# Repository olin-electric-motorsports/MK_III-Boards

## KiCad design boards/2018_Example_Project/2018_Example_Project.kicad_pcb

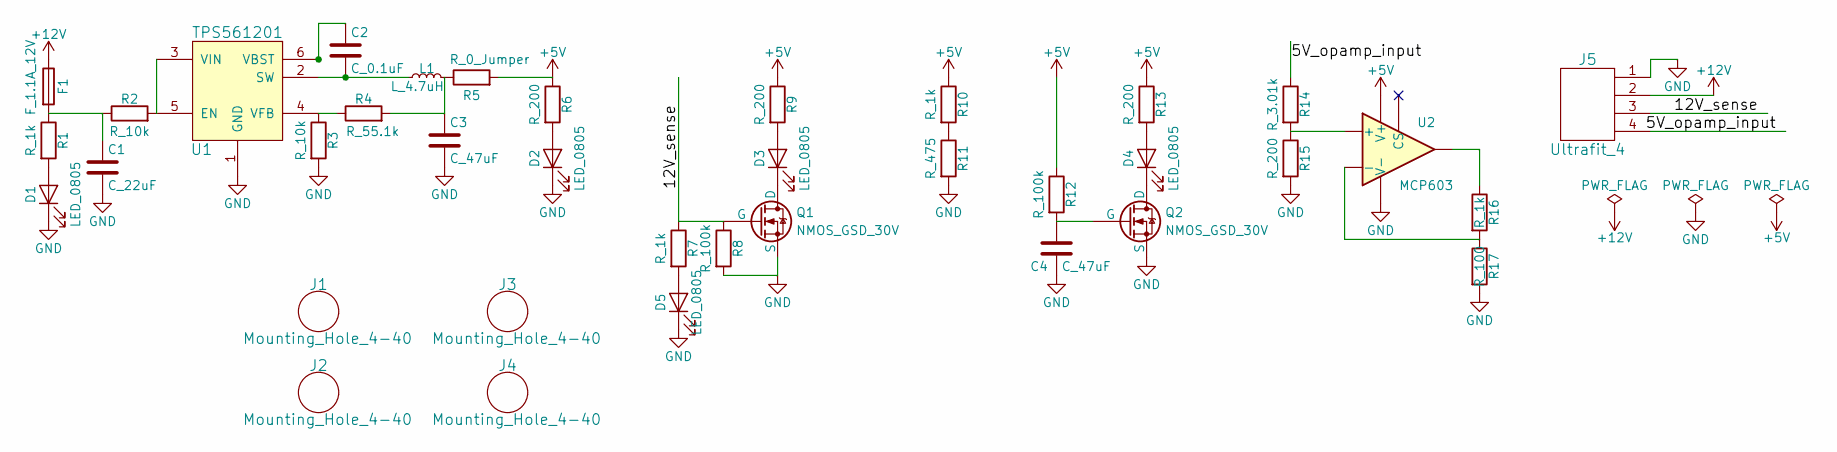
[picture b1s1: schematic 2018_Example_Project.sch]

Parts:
C1: C_22uF; C_1206; MPN 1276-2725-1-ND
C2: C_0.1uF; C_0805; MPN 478-3352-1-ND
C3, C4: C_47uF; C_0805; MPN 587-4280-1-ND
D1, D2, D3, D4, D5: LED_0805; MPN 475-1410-1-ND
F1: F_1.1A_12V; Fuse_SMD1206_Reflow; MPN F5764CT-ND
J1, J2, J3, J4: Mounting_Hole_4-40; MPN Value
J5: Ultrafit_4; MPN WM11574-ND
L1: L_4.7uH; 4.7uH_Inductor_OEM; MPN 445-6583-1-ND
Q1, Q2: NMOS_GSD_30V; SOT-23; MPN SSM3K333RLFCT-ND
R1, R7, R10, R16: R_1k; R_0805; MPN RNCP0805FTD1K00CT-ND
R2, R3: R_10k; R_0805; MPN CRS0805-FX-1002ELFCT-ND
R4: R_55.1k; R_0805; MPN 311-51.1KCRCT-ND
R5: R_0_Jumper; R_2512; MPN A121322CT-ND
R6, R9, R13, R15: R_200; R_0805; MPN RMCF0805JT200RCT-ND
R8, R12: R_100k; R_0805; MPN 311-100KCRCT-ND
R11: R_475; R_0805; MPN 311-475CRCT-ND
R14: R_3.01k; R_0805; MPN 311-3.01KCRCT-ND
R17: R_100; R_0805; MPN RNCP0805FTD100RCT-ND
U1: TPS561201; SOT-23-6; MPN TPS561201
U2: MCP603; SOT-23-6; MPN MCP603T-E/CHCT-ND

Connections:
+5V: R5.2, R6.1, R9.1, R10.1, R12.1, R13.1, U2.6 (V+)
+12V: F1.1, J5.2
/5V_opamp_input: J5.4, R14.1
/12V_sense: J5.3, Q1.1 (G), R7.1, R8.1
GND: C1.2, C3.2, C4.2, D1.1 (K), D2.1 (K), D5.1 (K), J5.1, Q1.2 (S), Q2.2 (S), R3.2, R8.2, R11.2, R15.2, R17.2, U1.1 (GND), U2.2 (V-)
unnamed: C1.1, F1.2, R1.1, R2.1
unnamed: C2.1, U1.6 (VBST)
unnamed: C2.2, L1.1, U1.2 (SW)
unnamed: C3.1, L1.2, R4.2, R5.1
unnamed: C4.1, Q2.1 (G), R12.2
unnamed: D1.2 (A), R1.2
unnamed: D2.2 (A), R6.2
unnamed: D3.1 (K), Q1.3 (D)
unnamed: D3.2 (A), R9.2
unnamed: D4.1 (K), Q2.3 (D)
unnamed: D4.2 (A), R13.2
unnamed: D5.2 (A), R7.2
unnamed: R2.2, U1.3 (VIN), U1.5 (EN)
unnamed: R3.1, R4.1, U1.4 (VFB)
unnamed: R10.2, R11.1
unnamed: R14.2, R15.1, U2.3 (+)
unnamed: R16.1, U2.1
unnamed: R16.2, R17.1, U2.4 (-)

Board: 2 copper layers, 37 parts (0 on the bottom side), 23 nets, no tracks yet.

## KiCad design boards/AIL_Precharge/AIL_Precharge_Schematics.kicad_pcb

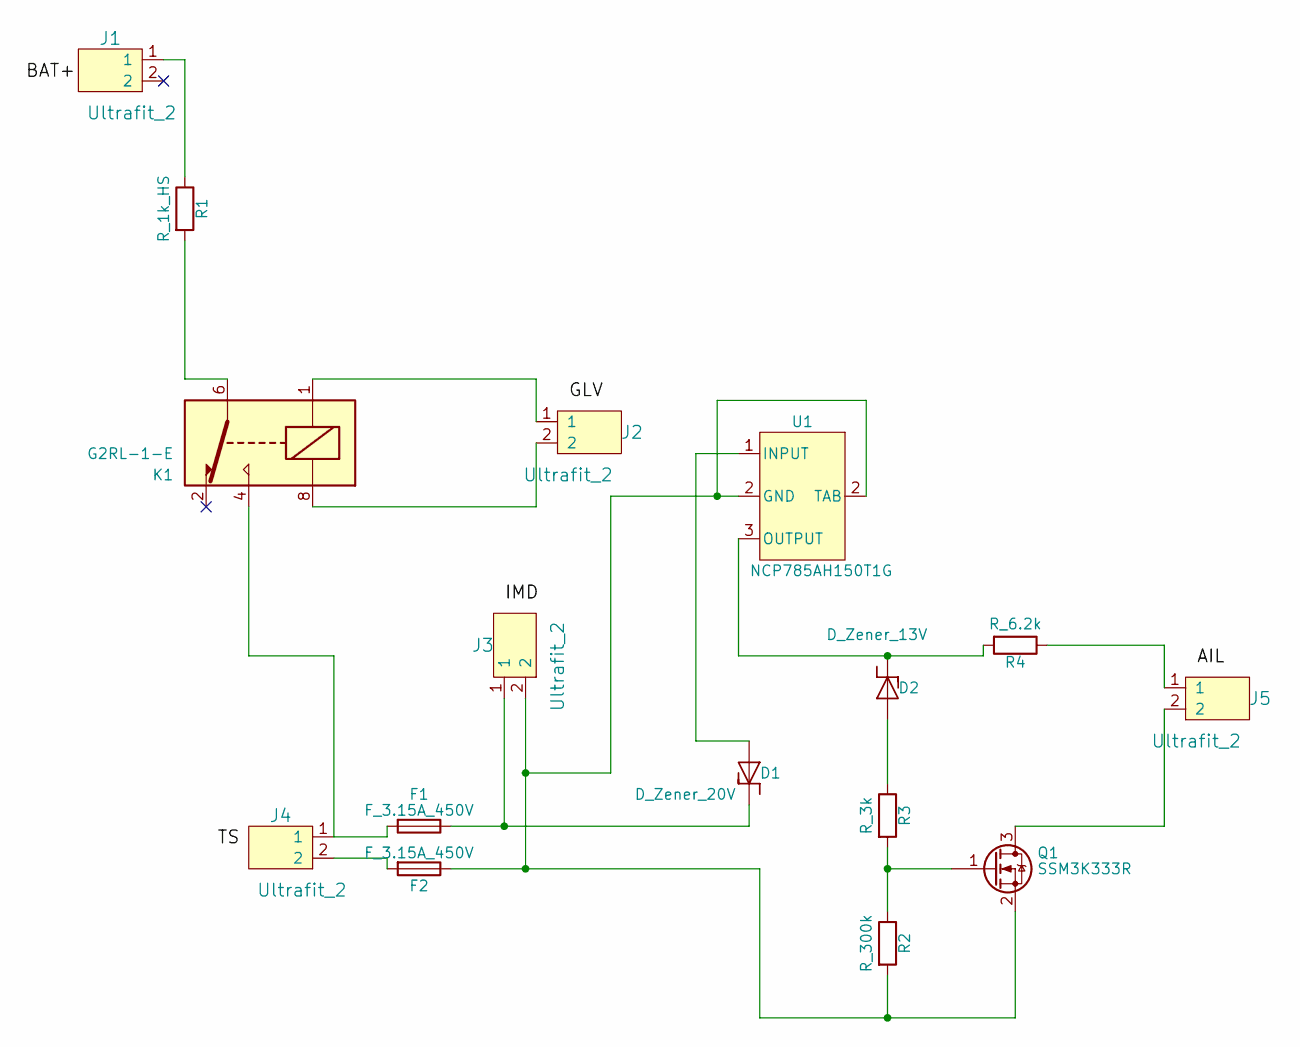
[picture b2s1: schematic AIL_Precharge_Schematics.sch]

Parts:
D1: D_Zener_20V; D_SOD-923; MPN CDZVT2R20BCT-ND
D2: D_Zener_13V; D_13V_Zener; MPN 1SMB5928BT3GOSCT-ND
F1, F2: F_3.15A_450V; Fuse_TE7_Littelfuse-807Series; MPN 80713150440
J1, J2, J3, J4, J5: Ultrafit_2; MPN WM11570-ND
K1: G2RL-1-E; Relay_SPDT_OMRON-G2RL-1-E; MPN Z2834-ND
Q1: SSM3K333R; SOT-23F; MPN SSM3K333RLFCT-ND
R1: R_1k_HS; R_1k_HS_TO247; MPN 696-1105-5-ND
R2: R_300k; R_0805_OEM; MPN P300KDACT-ND
R3: R_3k; R_0805_OEM; MPN RMCF0805FT3K00CT-ND
R4: R_6.2k; R_0805_OEM; MPN P6.20KCCT-ND
U1: NCP785AH150T1G; SOT-89-3; MPN NCP785AH150T1G

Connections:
unnamed: D1.1 (K), F1.1, J3.1
unnamed: D1.2 (A), U1.1 (INPUT)
unnamed: D2.1 (K), R4.2, U1.3 (OUTPUT)
unnamed: D2.2 (A), R3.1
unnamed: F1.2, J4.1, K1.4
unnamed: F2.1, J3.2, Q1.2 (S), R2.2, U1.2 (GND)
unnamed: F2.2, J4.2
unnamed: J1.1, R1.1
unnamed: J2.1, K1.1
unnamed: J2.2, K1.8
unnamed: J5.1, R4.1
unnamed: J5.2, Q1.3 (D)
unnamed: K1.6, R1.2
unnamed: Q1.1 (G), R2.1, R3.2

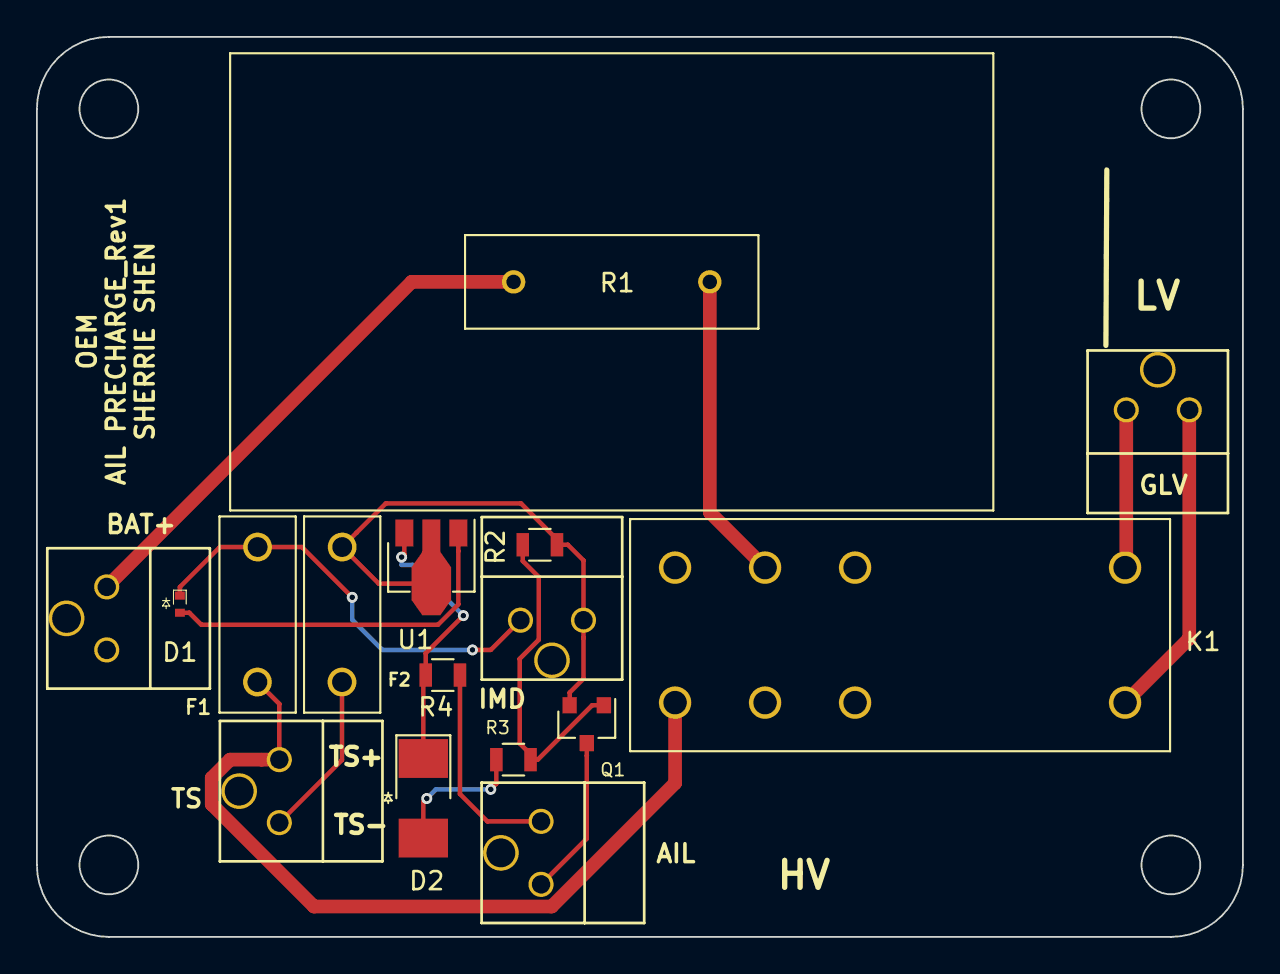
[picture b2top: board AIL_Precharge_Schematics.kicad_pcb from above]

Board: 2 copper layers, 67.0 x 50.0 mm, 16 parts (0 on the bottom side), 14 nets.

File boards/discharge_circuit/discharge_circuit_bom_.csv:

Component,Description,Part,References,Value,Footprint,Quantity Per PCB,Datasheet,MPN,MFN,PurchasingLink,Package,PurchasingLink2,MPN2
1,DIODE SCHOTTKY 100V 1A SOD123,D_Schottky_SOD123,D1,D_Schottky_SOD123,D_SOD-123W_OEM,1,https://assets.nexperia.com/documents/data-sheet/PMEG10010ELR.pdf,1727-2394-1-ND,Digi-Key,https://www.digikey.com/product-detail/en/nexperia-usa-inc/P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,,,
2,,F_3.15A_450V,F1 F2,F_3.15A_450V,Fuse_TE7_Littelfuse-807Series,2,http://www.mouser.com/ds/2/240/Littelfuse_Fuse_807_Datasheet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,80713150440,Mouser,https://www.mouser.com/ProductDetail/Littelfuse/80713150440/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,Value,,
3,ULTRAFIT CONN HDR 02CKT,Ultrafit_2,J2,Shutdown Circuit,Ultrafit_2,1,,WM11570-ND,Digi-Key,https://www.digikey.com/product-detail/en/molex-llc/17228611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,Value,,
4,Ultrafit 4 Pin Connector,Ultrafit_4,J3,TSMP/TSAL,Ultrafit_4,1,http://www.literature.molex.com/SQLImages/kelmscott/Molex/PD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,WM11574-ND,Digi-Key,https://www.digikey.com/products/en?keywords=WM11574-ND,Value,https://www.digikey.com/product-detail/en/molex-llc/17225610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,WM11564-ND
5,ULTRAFIT CONN HDR 02CKT,Ultrafit_2,J1,Unfused TS,Ultrafit_2,1,,WM11570-ND,Digi-Key,https://www.digikey.com/product-detail/en/molex-llc/17228611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,Value,,
6,"Omron G5G relay, Miniature Single Pole, SPDT, 10A",G2RL-1-E,K1,G2RL-1-E,Relay_SPDT_OMRON-G2RL-1-E,1,http://omronfs.omron.com/en_US/ecb/products/pdf/en-g2rl.pdf,Z2834-ND,Digi-Key,https://www.digikey.com/product-detail/en/omron-electronics-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,Value,,
7,Res 10k 1%,R_10k_HV,R2 R3,R_10k_HV,R_10K_HV,2,http://www.vishay.com/docs/28731/pacserie.pdf,PPC5D10.0KCT-ND,Digi-Key,https://www.digikey.com/products/en?keywords=PPC5D10.0KCT-ND,Value,,
8,3k ohm 100 w rating,R_3k_HS,R1,R_3k_HS,R_3k_HS_TO247,1,http://dpk3n3gg92jwt.cloudfront.net/domains/ohmite/pdf/acl_a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,AP101 3K J,Digi-Key,https://www.digikey.com/product-detail/en/ohmite/AP101-3K-J/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,Value,,





Component Groups:,8
Component Count:,10
Fitted Components:,10
Number of PCBs:,1
Total components:,10
Schematic Version:,
Schematic Date:,
BoM Date:,Thu 30 Nov 2017 09:13:59 PM EST
Schematic Source:,/home/william/Desktop/Formula/MK_III-Boards/boards/discharge_circuit/discharge_circuit.sch
KiCad Version:,Eeschema 4.0.7-e2-6376~58~ubuntu16.04.1

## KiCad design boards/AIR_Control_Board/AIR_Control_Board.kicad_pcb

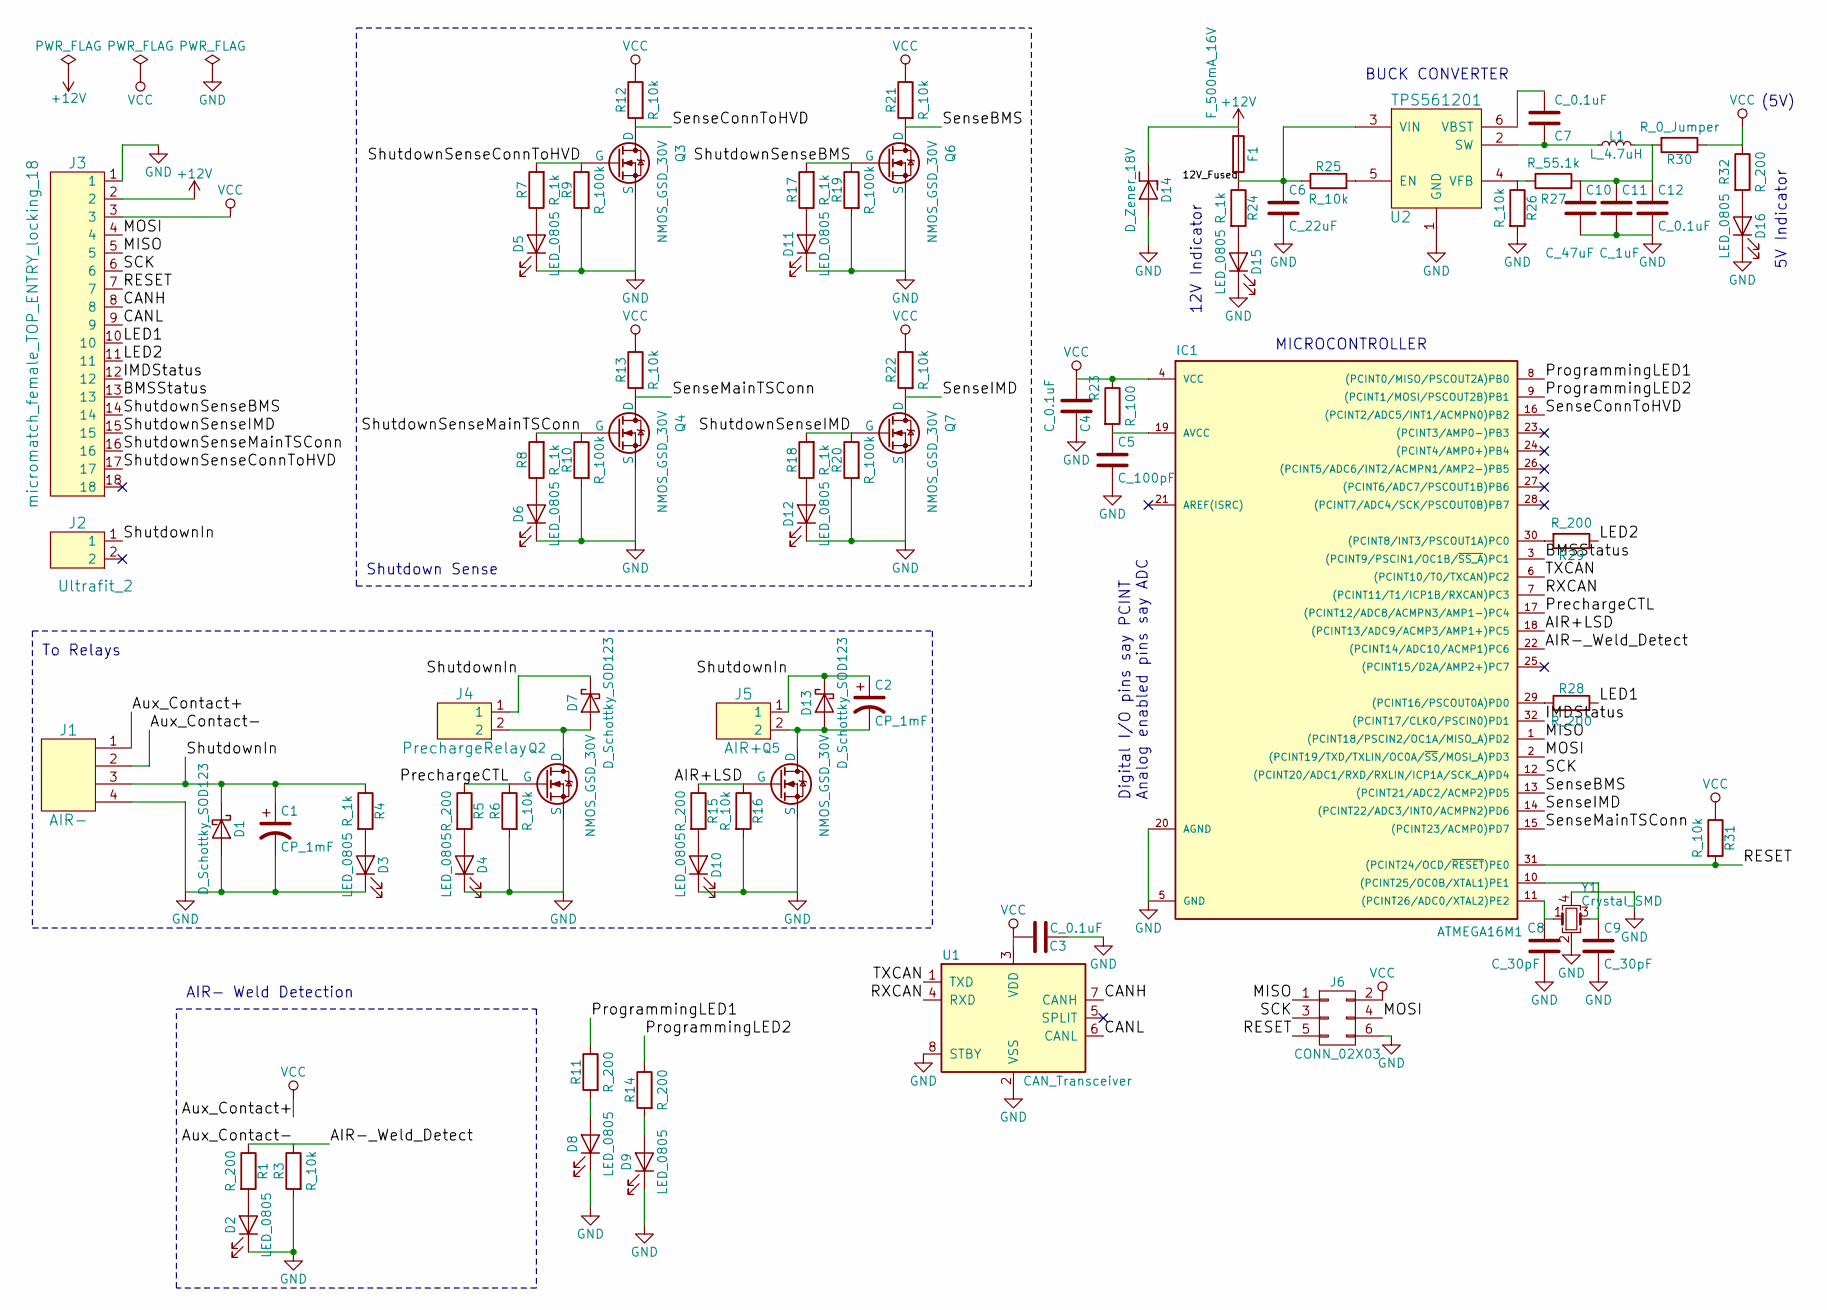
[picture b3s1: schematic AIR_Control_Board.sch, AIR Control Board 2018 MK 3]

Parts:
C1, C2: CP_1mF; C_Radial_D10_L13_P5_OEM; MPN 493-1305-ND
C3, C4, C7, C12: C_0.1uF; C_0805_OEM; MPN 478-3352-1-ND
C5: C_100pF; C_0805_OEM; MPN 399-1122-1-ND
C6: C_22uF; C_1206_OEM; MPN 1276-2725-1-ND
C8, C9: C_30pF; C_0805_OEM; MPN 1276-1130-1-ND
C10: C_47uF; C_0805_OEM; MPN 587-4280-1-ND
C11: C_1uF; C_0805_OEM; MPN 478-10487-1-ND
D1, D7, D13: D_Schottky_SOD123; D_SOD-123W_OEM; MPN 1727-2394-1-ND
D2, D3, D4, D5, D6, D8, D9, D10, D11, D12, D15, D16: LED_0805; LED_0805_OEM; MPN 475-1410-1-ND
D14: D_Zener_18V; DO-214AA; MPN SMBJ5355B-TPMSCT-ND
F1: F_500mA_16V; Fuse_1210; MPN 507-1786-1-ND
IC1: ATMEGA16M1; TQFP-32_7x7mm_Pitch0.8mm; MPN ATMEGA16M1-AU-ND
J1: AIR-; Ultrafit_4; MPN WM11574-ND
J2: Ultrafit_2; MPN WM11570-ND
J3: micromatch_female_TOP_ENTRY_locking_18; micromatch_female_vert_18; MPN A99500CT-ND
J4: PrechargeRelay; Ultrafit_2; MPN WM11570-ND
J5: AIR+; Ultrafit_2; MPN WM11570-ND
J6: CONN_02X03; Pin_Header_Straight_2x03; MPN 609-3234-ND
L1: L_4.7uH; 4.7uH_Inductor_OEM; MPN 445-6583-1-ND
Q2, Q3, Q4, Q5, Q6, Q7: NMOS_GSD_30V; SOT-23F; MPN SSM3K333RLFCT-ND
R1, R5, R11, R14, R15, R28, R29, R32: R_200; R_0805_OEM; MPN RMCF0805JT200RCT-ND
R3, R6, R12, R13, R16, R21, R22, R25, R26, R31: R_10k; R_0805_OEM; MPN CRS0805-FX-1002ELFCT-ND
R4, R7, R8, R17, R18, R24: R_1k; R_0805_OEM; MPN RNCP0805FTD1K00CT-ND
R9, R10, R19, R20: R_100k; R_0805_OEM; MPN 311-100KCRCT-ND
R23: R_100; R_0805_OEM; MPN RNCP0805FTD100RCT-ND
R27: R_55.1k; R_0805_OEM; MPN 311-51.1KCRCT-ND
R30: R_0_Jumper; R_2512_OEM; MPN A121322CT-ND
U1: CAN_Transceiver; SOIC-8_3.9x4.9mm_Pitch1.27mm_OEM; MPN MCP2561-E/SN-ND
U2: TPS561201; SOT-23-6_OEM; MPN TPS561201
Y1: Crystal_SMD; Crystal_SMD_FA238; MPN SER3686CT-ND

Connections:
+12V: D14.1 (K), F1.1, J3.2
/12V_Fused: C6.1, F1.2, R24.1, R25.1, U2.3 (VIN)
/AIR+LSD: IC1.18 ((PCINT13/ADC9/ACMP3/AMP1+)PC5), Q5.1 (G), R15.1, R16.1
/AIR-_Weld_Detect: IC1.22 ((PCINT14/ADC10/ACMP1)PC6), J1.2, R1.1, R3.1
/BMSStatus: IC1.3 ((PCINT9/PSCIN1/OC1B/~SS_A~)PC1), J3.13
/CANH: J3.8, U1.7 (CANH)
/CANL: J3.9, U1.6 (CANL)
/IMDStatus: IC1.32 ((PCINT17/CLKO/PSCIN0)PD1), J3.12
/LED1: J3.10, R28.2
/LED2: J3.11, R29.1
/MISO: IC1.1 ((PCINT18/PSCIN2/OC1A/MISO_A)PD2), J3.5, J6.1
/MOSI: IC1.2 ((PCINT19/TXD/TXLIN/OC0A/~SS~/MOSI_A)PD3), J3.4, J6.4
/PrechargeCTL: IC1.17 ((PCINT12/ADC8/ACMPN3/AMP1-)PC4), Q2.1 (G), R5.1, R6.1
/ProgrammingLED1: IC1.8 ((PCINT0/MISO/PSCOUT2A)PB0), R11.1
/ProgrammingLED2: IC1.9 ((PCINT1/MOSI/PSCOUT2B)PB1), R14.1
/RESET: IC1.31 ((PCINT24/OCD/~RESET~)PE0), J3.7, J6.5, R31.2
/RXCAN: IC1.7 ((PCINT11/T1/ICP1B/RXCAN)PC3), U1.4 (RXD)
/SCK: IC1.12 ((PCINT20/ADC1/RXD/RXLIN/ICP1A/SCK_A)PD4), J3.6, J6.3
/SenseBMS: IC1.13 ((PCINT21/ADC2/ACMP2)PD5), Q6.3 (D), R21.2
/SenseConnToHVD: IC1.16 ((PCINT2/ADC5/INT1/ACMPN0)PB2), Q3.3 (D), R12.2
/SenseIMD: IC1.14 ((PCINT22/ADC3/INT0/ACMPN2)PD6), Q7.3 (D), R22.2
/SenseMainTSConn: IC1.15 ((PCINT23/ACMP0)PD7), Q4.3 (D), R13.2
/ShutdownIn: C1.1, C2.1, D1.1 (K), D7.1 (K), D13.1 (K), J1.3, J2.1, J4.1, J5.1, R4.1
/ShutdownSenseBMS: J3.14, Q6.1 (G), R17.2, R19.1
/ShutdownSenseConnToHVD: J3.17, Q3.1 (G), R7.2, R9.1
/ShutdownSenseIMD: J3.15, Q7.1 (G), R18.2, R20.1
/ShutdownSenseMainTSConn: J3.16, Q4.1 (G), R8.2, R10.1
/TXCAN: IC1.6 ((PCINT10/T0/TXCAN)PC2), U1.1 (TXD)
GND: C1.2, C3.2, C4.2, C5.2, C6.2, C8.2, C9.2, C10.2, C11.2, C12.2, D1.2 (A), D2.1 (K), D3.1 (K), D4.1 (K), D5.1 (K), D6.1 (K), D8.1 (K), D9.1 (K), D10.1 (K), D11.1 (K), D12.1 (K), D14.2 (A), D15.1 (K), D16.1 (K), IC1.5 (GND), IC1.20 (AGND), J1.4, J3.1, J6.6, Q2.2 (S), Q3.2 (S), Q4.2 (S), Q5.2 (S), Q6.2 (S), Q7.2 (S), R3.2, R6.2, R9.2, R10.2, R16.2, R19.2, R20.2, R26.2, U1.2 (VSS), U1.8 (STBY), U2.1 (GND), Y1.2, Y1.4
unnamed: C2.2, D13.2 (A), J5.2, Q5.3 (D)
unnamed: C5.1, IC1.19 (AVCC), R23.2
unnamed: C7.1, U2.6 (VBST)
unnamed: C7.2, L1.1, U2.2 (SW)
unnamed: C8.1, IC1.11 ((PCINT26/ADC0/XTAL2)PE2), Y1.1
unnamed: C9.1, IC1.10 ((PCINT25/OC0B/XTAL1)PE1), Y1.3
unnamed: C10.1, C11.1, C12.1, L1.2, R27.2, R30.2
unnamed: D2.2 (A), R1.2
unnamed: D3.2 (A), R4.2
unnamed: D4.2 (A), R5.2
unnamed: D5.2 (A), R7.1
unnamed: D6.2 (A), R8.1
unnamed: D7.2 (A), J4.2, Q2.3 (D)
unnamed: D8.2 (A), R11.2
unnamed: D9.2 (A), R14.2
unnamed: D10.2 (A), R15.2
unnamed: D11.2 (A), R17.1
unnamed: D12.2 (A), R18.1
unnamed: D15.2 (A), R24.2
unnamed: D16.2 (A), R32.2
unnamed: IC1.29 ((PCINT16/PSCOUT0A)PD0), R28.1
unnamed: IC1.30 ((PCINT8/INT3/PSCOUT1A)PC0), R29.2
unnamed: R25.2, U2.5 (EN)
unnamed: R26.1, R27.1, U2.4 (VFB)
VCC: C3.1, C4.1, IC1.4 (VCC), J1.1, J3.3, J6.2, R12.1, R13.1, R21.1, R22.1, R23.1, R30.1, R31.1, R32.1, U1.3 (VDD)

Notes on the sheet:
BUCK CONVERTER
12V Indicator
5V Indicator
(5V)
MICROCONTROLLER
Digital I/O pins say PCINT Analog enabled pins say ADC
To Relays
Shutdown Sense
AIR- Weld Detection

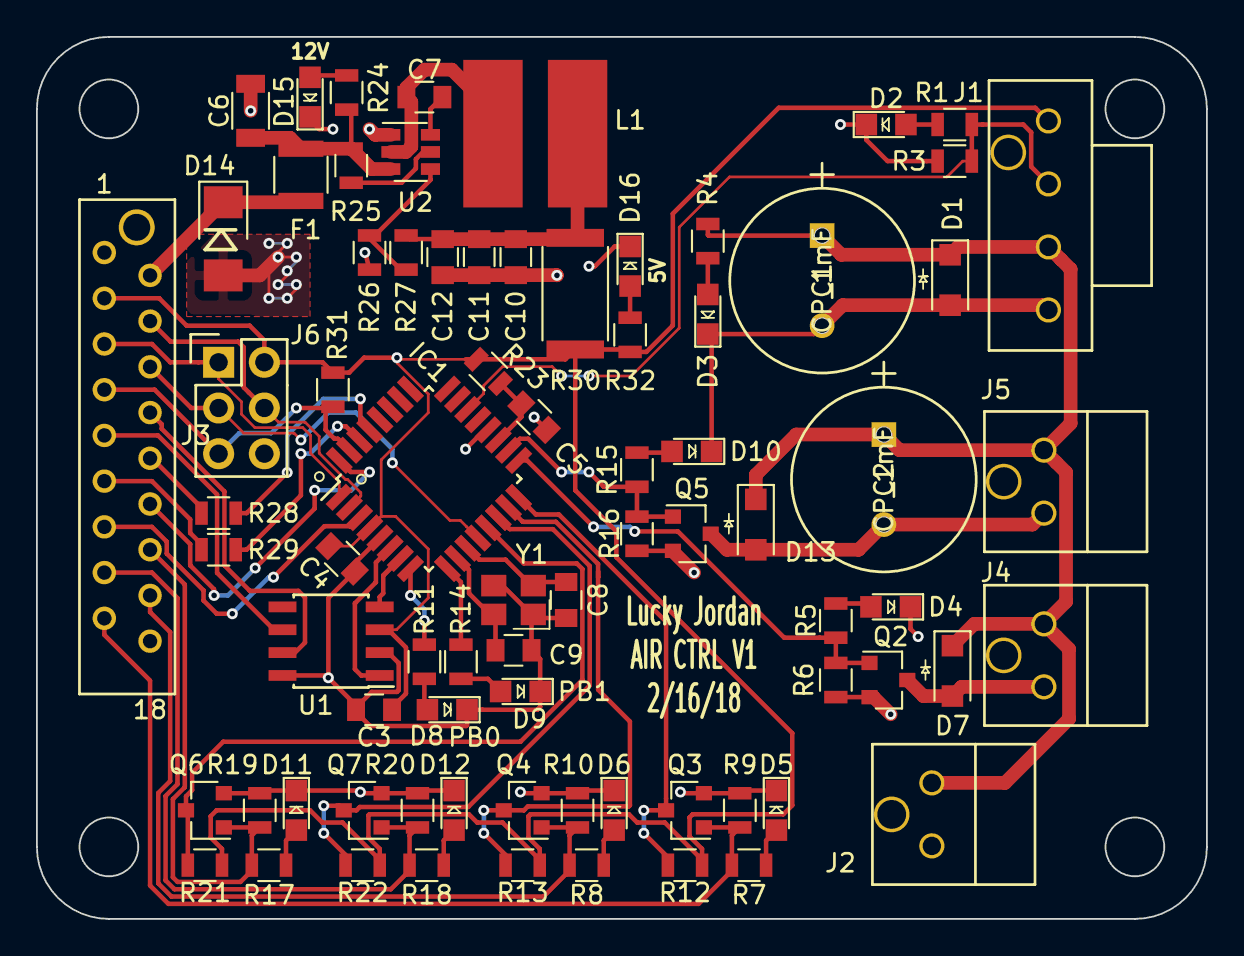
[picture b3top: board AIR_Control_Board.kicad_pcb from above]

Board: 2 copper layers, 65.0 x 49.0 mm, 77 parts (0 on the bottom side), 54 nets.

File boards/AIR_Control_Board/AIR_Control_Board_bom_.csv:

Component,Description,Part,References,Value,Footprint,Quantity Per PCB,Datasheet,Package,MPN,Purchasing Link,MFN,PurchasingLink,PurchasingLink2,MPN2
1,,CP_1mF,C1 C2,CP_1mF,C_Radial_D10_L13_P5_OEM,2,http://nichicon-us.com/english/products/pdfs/e-uvz.pdf,"Radial, Can",493-1305-ND,https://www.digikey.com/products/en?keywords=493-1305-ND,Digi-Key,,,
2,Cap 50V 0.1uF 10% 0805,C_0.1uF,C3 C4 C7 C12,C_0.1uF,C_0805_OEM,4,http://datasheets.avx.com/X7RDielectric.pdf,Value,478-3352-1-ND,,Digi-Key,https://www.digikey.com/products/en?keywords=478-3352-1-ND,,
3,Cap 50V 100pF 5% 0805,C_100pF,C5,C_100pF,C_0805_OEM,1,https://content.kemet.com/datasheets/KEM_C1003_C0G_SMD.pdf,Value,399-1122-1-ND,,Digi-Key,https://www.digikey.com/product-detail/en/kemet/C0805C101J5G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,,
4,CAP CER 1UF 25V X7R 0805,C_1uF,C11,C_1uF,C_0805_OEM,1,http://datasheets.avx.com/X7RDielectric.pdf,Value,478-10487-1-ND,,Digi-Key,https://www.digikey.com/product-detail/en/avx-corporation/08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,,
5,Unpolarized capacitor,C_22uF,C6,C_22uF,C_1206_OEM,1,http://www.samsungsem.com/kr/support/product-search/mlcc/__i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,Value,1276-2725-1-ND,,Digi-Key,https://www.digikey.com/products/en?keywords=1276-2725-1-ND,,
6,Cap 50V 30pF 5% 0805,C_30pF,C8 C9,C_30pF,C_0805_OEM,2,https://media.digikey.com/pdf/Data%20Sheets/Samsung%20PDFs/C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,Value,1276-1130-1-ND,,Digi-Key,https://www.digikey.com/product-detail/en/samsung-electro-me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,,
7,CAP CER 47UF 6.3V X5R 0805,C_47uF,C10,C_47uF,C_0805_OEM,1,http://www.yuden.co.jp/productdata/catalog/en/mlcc_all_e.pdf,Value,587-4280-1-ND,,Digi-Key,https://www.digikey.com/product-detail/en/taiyo-yuden/JMK212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,,
8,DIODE SCHOTTKY 100V 1A SOD123,D_Schottky_SOD123,D1 D7 D13,D_Schottky_SOD123,D_SOD-123W_OEM,3,https://assets.nexperia.com/documents/data-sheet/PMEG10010ELR.pdf,,1727-2394-1-ND,,Digi-Key,https://www.digikey.com/product-detail/en/nexperia-usa-inc/P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,,
9,DIODE ZENER 18V 5W DO214AA,D_Zener_18V,D14,D_Zener_18V,DO-214AA,1,http://www.mccsemi.com/up_pdf/SMBJ5338B-SMBJ5388B(SMB).pdf,DO-214AA (SMB),SMBJ5355B-TPMSCT-ND,,Digi-Key,https://www.digikey.com/products/en?keywords=SMBJ5355B-TPMSCT-ND,,
10,LED_0805,LED_0805,D2 D3 D4 D5 D6 D8 D9 D10 D11 D12 D15 D16,LED_0805,LED_0805_OEM,12,http://www.osram-os.com/Graphics/XPic9/00078860_0.pdf,Value,475-1410-1-ND,,Digi-Key,https://www.digikey.com/products/en?keywords=475-1410-1-ND,,
11,PTC Fuse 16V 500mA,F_500mA_16V,F1,F_500mA_16V,Fuse_1210,1,https://belfuse.com/resources/CircuitProtection/datasheets/0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,Value,507-1786-1-ND,,Digi-Key,https://www.digikey.com/product-detail/en/bel-fuse-inc/0ZCH0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,,
12,"TQFP32, 16k Flash, 1k SRAM, 512B EEPROM, CAN",ATMEGA16M1,IC1,ATMEGA16M1,TQFP-32_7x7mm_Pitch0.8mm,1,http://www.atmel.com/Images/Atmel-8209-8-bit%20AVR%20ATmega1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,Value,ATMEGA16M1-AU-ND,,Digi-Key,https://www.digikey.com/product-detail/en/atmel/ATMEGA16M1-A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,,
13,,Ultrafit_2-RESCUE-AIR_Control_Board,J5,AIR+,Ultrafit_2,1,,Value,WM11570-ND,,Digi-Key,https://www.digikey.com/product-detail/en/molex-llc/17228611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,,
14,Ultrafit 4 Pin Connector,Ultrafit_4,J1,AIR-,Ultrafit_4,1,http://www.literature.molex.com/SQLImages/kelmscott/Molex/PD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,Value,WM11574-ND,,Digi-Key,https://www.digikey.com/products/en?keywords=WM11574-ND,https://www.digikey.com/product-detail/en/molex-llc/17225610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,WM11564-ND
15,"Connector, double row, 02x03",CONN_02X03,J6,CONN_02X03,Pin_Header_Straight_2x03,1,http://portal.fciconnect.com/Comergent//fci/drawing/67996.pdf,Value,609-3234-ND,,Digi-Key,https://www.digikey.com/product-detail/en/amphenol-fci/67997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,,
16,,Ultrafit_2-RESCUE-AIR_Control_Board,J4,PrechargeRelay,Ultrafit_2,1,,Value,WM11570-ND,,Digi-Key,https://www.digikey.com/product-detail/en/molex-llc/17228611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,,
17,ULTRAFIT CONN HDR 02CKT,Ultrafit_2,J2,Ultrafit_2,Ultrafit_2,1,,Value,WM11570-ND,,Digi-Key,https://www.digikey.com/product-detail/en/molex-llc/17228611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,,
18,CONN FMALE-ON-BRD 18POS VERT T/H,micromatch_female_TOP_ENTRY_locking_18,J3,micromatch_female_TOP_ENTRY_locking_18,micromatch_female_vert_18,1,,Value,A99500CT-ND,,Digi-Key,https://www.digikey.com/product-detail/en/te-connectivity-am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,,
19,Inductor 4.7uH 4.4A,L_4.7uH,L1,L_4.7uH,4.7uH_Inductor_OEM,1,https://product.tdk.com/info/en/documents/wdcatalog/withdraw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,Value,445-6583-1-ND,,Digi-Key,https://www.digikey.com/product-detail/en/tdk-corporation/VL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,,
20,N-channel MOSFET,NMOS_GSD_30V,Q2 Q3 Q4 Q5 Q6 Q7,NMOS_GSD_30V,SOT-23F,6,https://www.digikey.com/products/en?keywords=SSM3K333RLFCT-ND,Value,SSM3K333RLFCT-ND,,Digi-Key,https://www.digikey.com/products/en?keywords=SSM3K333RLFCT-ND,,
21,Res 0 2512 3W Jumper,R_0_Jumper,R30,R_0_Jumper,R_2512_OEM,1,http://www.te.com/commerce/DocumentDelivery/DDEController?Ac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,Value,A121322CT-ND,,Digi-Key,https://www.digikey.com/products/en?keywords=A121322CT-ND,,
22,Res 100 1%,R_100,R23,R_100,R_0805_OEM,1,https://www.seielect.com/Catalog/SEI-rncp.pdf,Value,RNCP0805FTD100RCT-ND,,Digi-Key,https://www.digikey.com/products/en?keywords=RNCP0805FTD100RCT-ND,,
23,Res 100k 1%,R_100k,R9 R10 R19 R20,R_100k,R_0805_OEM,4,http://www.yageo.com.tw/exep/pages/download/literatures/PYu-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,Value,311-100KCRCT-ND,,Digi-Key,https://www.digikey.com/products/en?keywords=311-100KCRCT-ND,,
24,Res 10k 1%,R_10k,R3 R6 R12 R13 R16 R21 R22 R25 R26 R31,R_10k,R_0805_OEM,10,http://www.bourns.com/data/global/pdfs/CRS.pdf,Value,CRS0805-FX-1002ELFCT-ND,,Digi-Key,https://www.digikey.com/products/en?keywords=CRS0805-FX-1002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,,
25,Res 1k 1%,R_1k,R4 R7 R8 R17 R18 R24,R_1k,R_0805_OEM,6,https://www.seielect.com/Catalog/SEI-rncp.pdf,Value,RNCP0805FTD1K00CT-ND,,Digi-Key,https://www.digikey.com/products/en?keywords=RNCP0805FTD1K00CT-ND,,
26,Res 200 5%,R_200,R1 R5 R11 R14 R15 R28 R29 R32,R_200,R_0805_OEM,8,https://www.seielect.com/Catalog/SEI-RMCF_RMCP.pdf,Value,RMCF0805JT200RCT-ND,,Digi-Key,https://www.digikey.com/products/en?keywords=RMCF0805JT200RCT-ND,,
27,Res 55.1k 1%,R_55.1k,R27,R_55.1k,R_0805_OEM,1,http://www.yageo.com.tw/exep/pages/download/literatures/PYu-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,Value,311-51.1KCRCT-ND,,Digi-Key,https://www.digikey.com/products/en?keywords=311-51.1KCRCT-ND,,
28,"High-Speed CAN Transceiver, 1Mbps, 5V supply, SPLIT pin, -40C to +125C, SOIC8 package",CAN_Transceiver,U1,CAN_Transceiver,SOIC-8_3.9x4.9mm_Pitch1.27mm_OEM,1,http://www.microchip.com/mymicrochip/filehandler.aspx?ddocna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,Value,MCP2561-E/SN-ND,,Digi-Key,https://www.digikey.com/products/en?keywords=mcp2561-e%2Fsn,,
29,4.5V - 17V Input 1A Synchronous Buck Converter,TPS561201,U2,TPS561201,SOT-23-6_OEM,1,http://www.ti.com/lit/ds/symlink/tps561201.pdf,Value,TPS561201,,Digi-Key,https://www.digikey.com/products/en?keywords=296-46928-1-ND,,
30,"Two pin crystal, two ground/package pins (pin2 and 3) small symbol",Crystal_SMD,Y1,Crystal_SMD,Crystal_SMD_FA238,1,https://support.epson.biz/td/api/doc_check.php?dl=brief_FA-2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,Value,SER3686CT-ND,,Digi-Key,https://www.digikey.com/products/en?keywords=SER3686CT-ND,,





Component Groups:,30
Component Count:,77
Fitted Components:,77
Number of PCBs:,1
Total components:,77
Schematic Version:,
Schematic Date:,
BoM Date:,2/19/2018 1:06:32 PM
Schematic Source:,C:/Users/ljordan/Desktop/Olin/Formula/2017-18/MK_III-Boards/boards/AIR_Control_Board/AIR_Control_Board.sch
KiCad Version:,Eeschema 4.0.7

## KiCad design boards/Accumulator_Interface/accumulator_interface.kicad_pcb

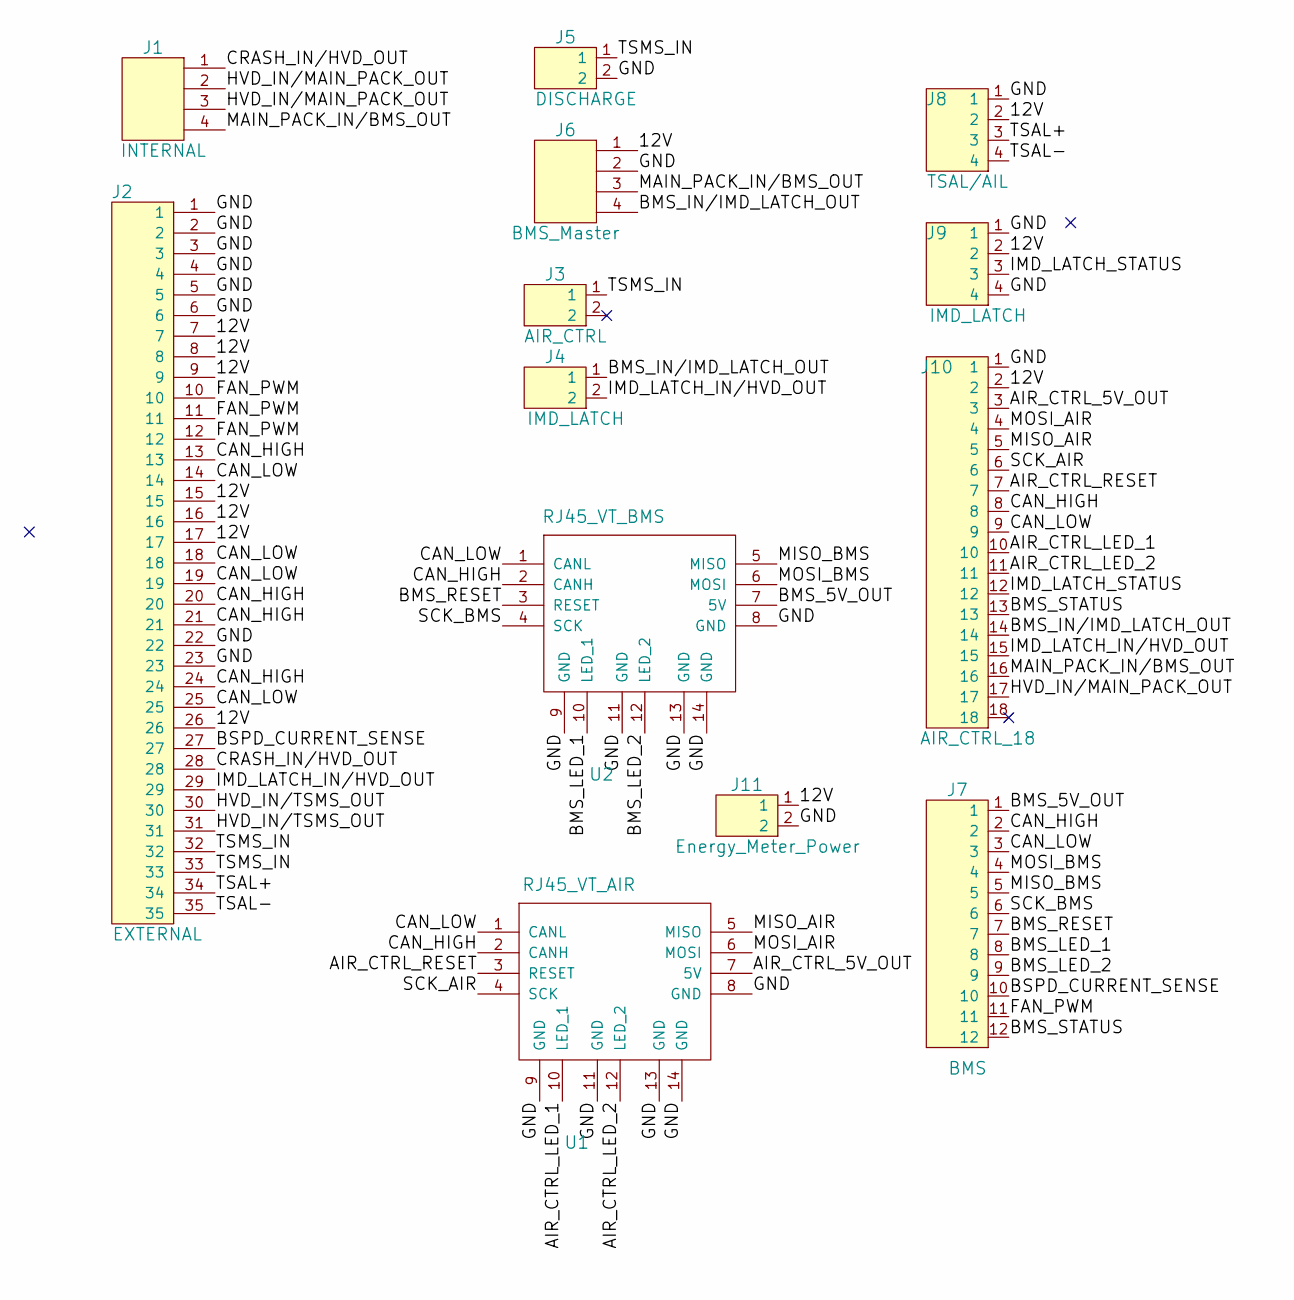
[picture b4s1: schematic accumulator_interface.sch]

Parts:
J1: INTERNAL; Ultrafit_4; MPN WM11574-ND
J2: EXTERNAL; Ampseal_35
J3: AIR_CTRL; Ultrafit_2; MPN WM11570-ND
J4: IMD_LATCH; Ultrafit_2; MPN WM11570-ND
J5: DISCHARGE; Ultrafit_2; MPN WM11570-ND
J6: BMS_Master; Ultrafit_4; MPN WM11574-ND
J7: BMS; micromatch_female_vert_12; MPN A99503CT-ND
J8: TSAL/AIL; micromatch_female_vert_4; MPN 338068-4
J9: IMD_LATCH; micromatch_female_vert_4; MPN 338068-4
J10: AIR_CTRL_18; micromatch_female_vert_18; MPN A99500CT-ND
J11: Energy_Meter_Power; Ultrafit_2; MPN WM11570-ND
U1: RJ45_VT_AIR; RJ45-Vertical
U2: RJ45_VT_BMS; RJ45-Vertical

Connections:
/12V: J2.7, J2.8, J2.9, J2.15, J2.16, J2.17, J2.26, J6.1, J8.2, J9.2, J10.2, J11.1
/AIR_CTRL_5V_OUT: J10.3, U1.7 (5V)
/AIR_CTRL_LED_1: J10.10, U1.10 (LED_1)
/AIR_CTRL_LED_2: J10.11, U1.12 (LED_2)
/AIR_CTRL_RESET: J10.7, U1.3 (RESET)
/BMS_5V_OUT: J7.1, U2.7 (5V)
/BMS_IN/IMD_LATCH_OUT: J4.1, J6.4, J10.14
/BMS_LED_1: J7.8, U2.10 (LED_1)
/BMS_LED_2: J7.9, U2.12 (LED_2)
/BMS_RESET: J7.7, U2.3 (RESET)
/BMS_STATUS: J7.12, J10.13
/BSPD_CURRENT_SENSE: J2.27, J7.10
/CAN_HIGH: J2.13, J2.20, J2.21, J2.24, J7.2, J10.8, U1.2 (CANH), U2.2 (CANH)
/CAN_LOW: J2.14, J2.18, J2.19, J2.25, J7.3, J10.9, U1.1 (CANL), U2.1 (CANL)
/CRASH_IN/HVD_OUT: J1.1, J2.28
/FAN_PWM: J2.10, J2.11, J2.12, J7.11
/GND: J2.1, J2.2, J2.3, J2.4, J2.5, J2.6, J2.22, J2.23, J5.2, J6.2, J8.1, J9.1, J9.4, J10.1, J11.2, U1.8 (GND), U1.9 (GND), U1.11 (GND), U1.13 (GND), U1.14 (GND), U2.8 (GND), U2.9 (GND), U2.11 (GND), U2.13 (GND), U2.14 (GND)
/HVD_IN/MAIN_PACK_OUT: J1.2, J1.3, J10.17
/HVD_IN/TSMS_OUT: J2.30, J2.31
/IMD_LATCH_IN/HVD_OUT: J2.29, J4.2, J10.15
/IMD_LATCH_STATUS: J9.3, J10.12
/MAIN_PACK_IN/BMS_OUT: J1.4, J6.3, J10.16
/MISO_AIR: J10.5, U1.5 (MISO)
/MISO_BMS: J7.5, U2.5 (MISO)
/MOSI_AIR: J10.4, U1.6 (MOSI)
/MOSI_BMS: J7.4, U2.6 (MOSI)
/SCK_AIR: J10.6, U1.4 (SCK)
/SCK_BMS: J7.6, U2.4 (SCK)
/TSAL+: J2.34, J8.3
/TSAL-: J2.35, J8.4
/TSMS_IN: J2.32, J2.33, J3.1, J5.1

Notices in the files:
parts and their libraries:
Copyright 2016 Accelerated Designs. All rights reserved.
